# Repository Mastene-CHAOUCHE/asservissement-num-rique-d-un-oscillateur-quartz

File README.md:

# asservissement-num-rique-d-un-oscillateur-quartz

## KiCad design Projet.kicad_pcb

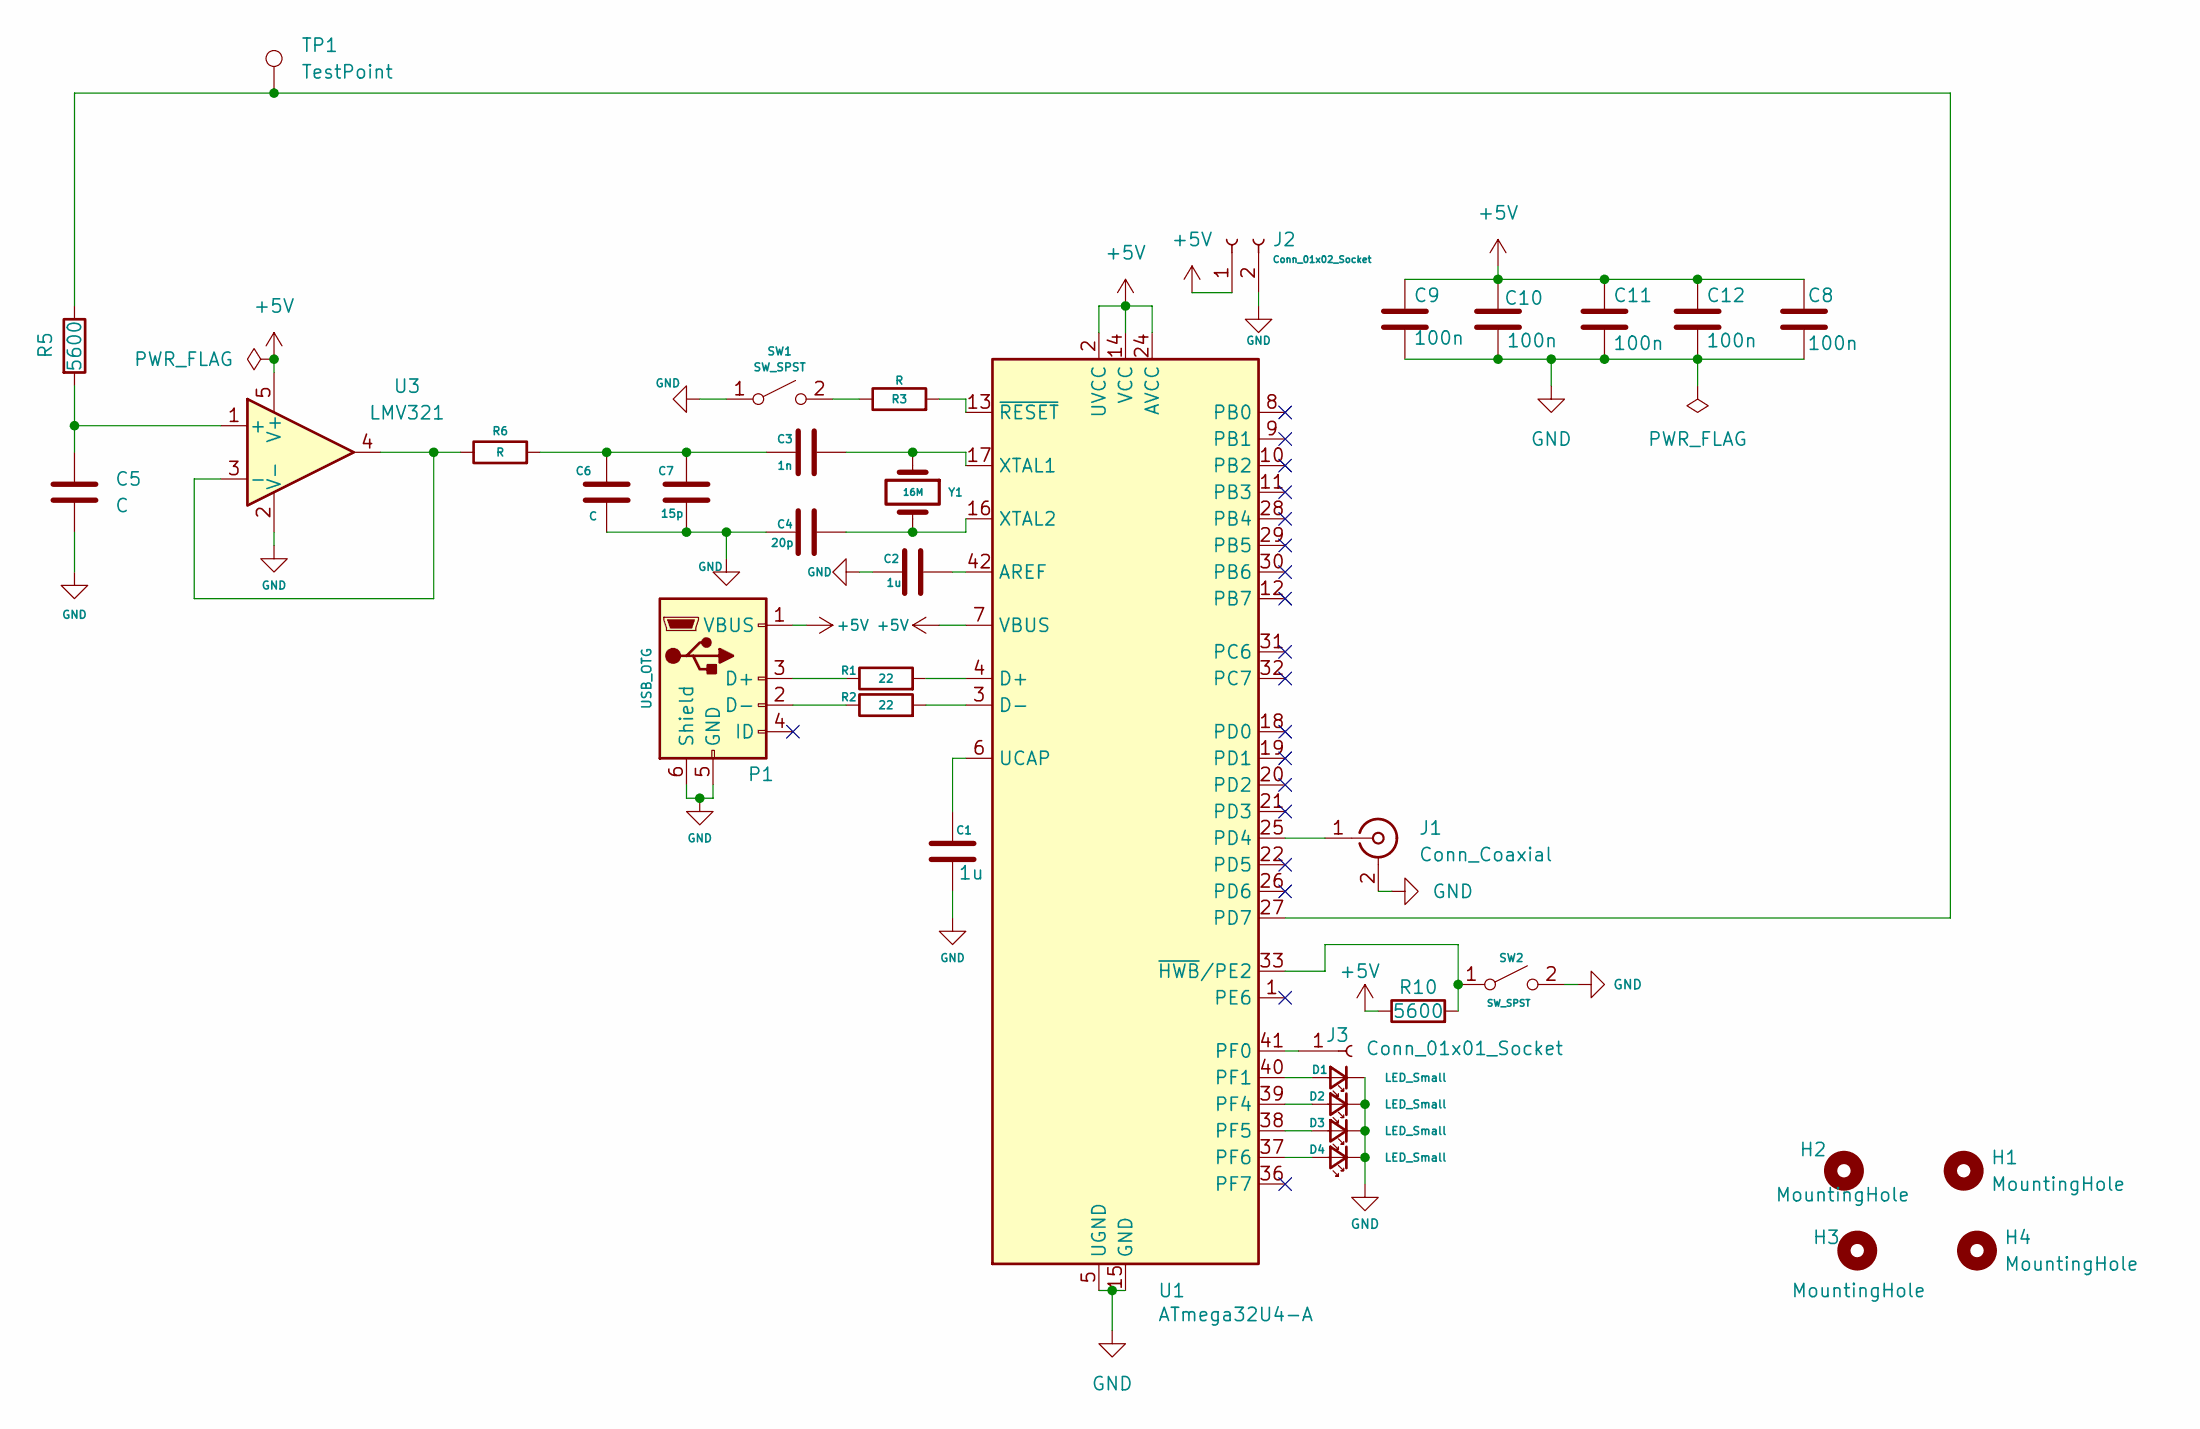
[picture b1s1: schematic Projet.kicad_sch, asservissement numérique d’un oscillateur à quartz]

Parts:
C1, C2: 1u; C_0805_2012Metric_Pad1.18x1.45mm_HandSolder
C3: 1n; C_0805_2012Metric_Pad1.18x1.45mm_HandSolder
C4: 20p; C_0805_2012Metric_Pad1.18x1.45mm_HandSolder
C5, C6: C; C_0805_2012Metric_Pad1.18x1.45mm_HandSolder
C7: 15p; C_0805_2012Metric_Pad1.18x1.45mm_HandSolder
C8, C9, C10, C11, C12: 100n; C_0805_2012Metric_Pad1.18x1.45mm_HandSolder
D1, D2, D3, D4: LED_Small; LED_1206_3216Metric_Pad1.42x1.75mm_HandSolder
H1, H2, H3, H4: MountingHole; MountingHole_3mm
J1: Conn_Coaxial; SMA_Amphenol_132134_Vertical
J2: Conn_01x02_Socket; PinHeader_1x02_P2.54mm_Vertical
J3: Conn_01x01_Socket; PinHeader_1x01_P2.54mm_Vertical
P1: USB_OTG; USB_Mini-B_Lumberg_2486_01_Horizontal
R1, R2: 22; R_0805_2012Metric_Pad1.20x1.40mm_HandSolder
R3, R6: R; R_0805_2012Metric_Pad1.20x1.40mm_HandSolder
R5, R10: 5600; R_0805_2012Metric_Pad1.20x1.40mm_HandSolder
SW1, SW2: SW_SPST; SW_PUSH_6mm
TP1: TestPoint; TestPoint_Pad_1.0x1.0mm
U1: ATmega32U4-A; TQFP-44_10x10mm_P0.8mm
U3: LMV321; SOT-23-5_HandSoldering
Y1: 16M; Crystal_SMD_5032-2Pin_5.0x3.2mm_HandSoldering

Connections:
+5V: C8.1, C9.1, C10.1, C11.1, C12.1, J2.1, P1.1 (VBUS), R10.1, U1.2 (UVCC), U1.7 (VBUS), U1.14 (VCC), U1.24 (AVCC), U1.34 (VCC), U1.44 (AVCC), U3.5 (V+)
GND: C1.2, C2.1, C4.1, C5.2, C6.2, C7.2, C8.2, C9.2, C10.2, C11.2, C12.2, D1.1 (K), D2.1 (K), D3.1 (K), D4.1 (K), J1.2 (Ext), J2.2, P1.5 (GND), P1.6 (Shield), SW1.1 (A), SW2.2 (B), U1.5 (UGND), U1.15 (GND), U1.23 (GND), U1.35 (GND), U1.43 (GND), U3.2 (V-)
unnamed: C3.2, C6.1, C7.1, R6.2
unnamed: D1.2 (A), U1.40 (PF1)
unnamed: D2.2 (A), U1.39 (PF4)
unnamed: D3.2 (A), U1.38 (PF5)
unnamed: D4.2 (A), U1.37 (PF6)
unnamed: J1.1 (In), U1.25 (PD4)
unnamed: J3.1, U1.41 (PF0)
unnamed: P1.3 (D+), R1.1
unnamed: P1.2 (D-), R2.1
unnamed: R3.1, SW1.2 (B)
unnamed: R10.2, SW2.1 (A), U1.33 (~HWB/PE2)
unnamed: C2.2, U1.42 (AREF)
unnamed: R1.2, U1.4 (D+)
unnamed: R2.2, U1.3 (D-)
unnamed: R5.1, TP1.1, U1.27 (PD7)
unnamed: C1.1, U1.6 (UCAP)
unnamed: C3.1, U1.17 (XTAL1), Y1.1
unnamed: C4.2, U1.16 (XTAL2), Y1.2
unnamed: R3.2, U1.13 (~RESET)
unnamed: C5.1, R5.2, U3.1 (+)
unnamed: R6.1, U3.3 (-), U3.4

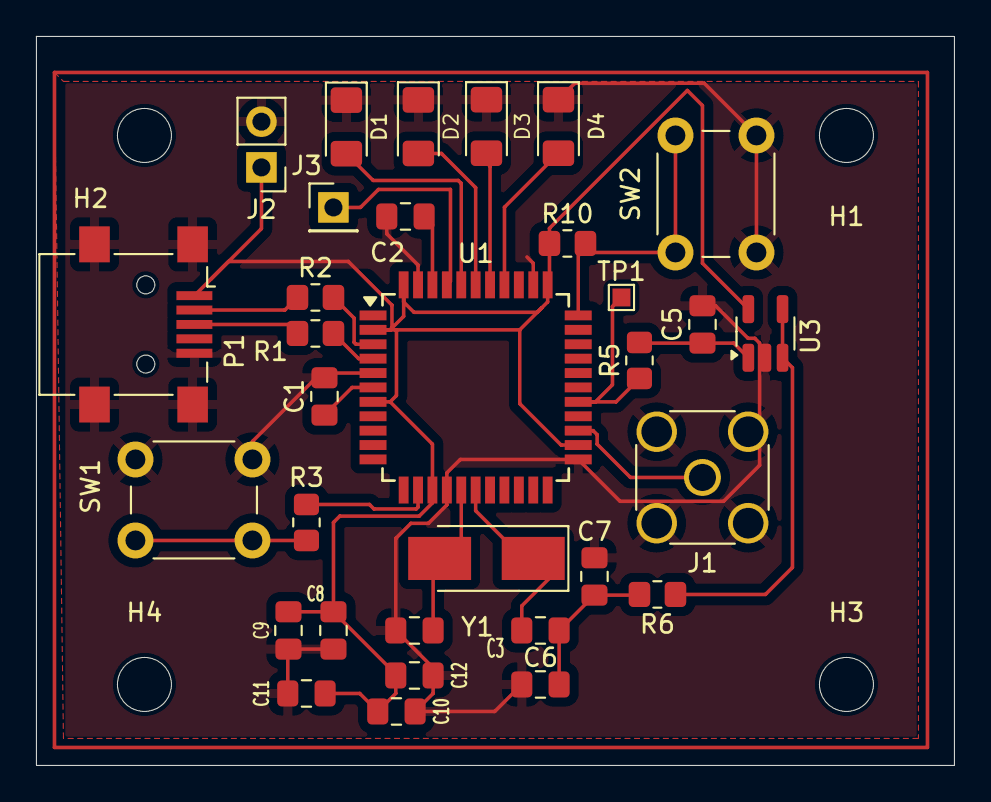
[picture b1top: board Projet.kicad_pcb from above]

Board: 2 copper layers, 51.0 x 40.5 mm, 36 parts (0 on the bottom side), 23 nets.

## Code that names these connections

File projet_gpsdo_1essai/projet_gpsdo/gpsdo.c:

#define F_CPU 16000000UL
#include <avr/io.h> //E/S ex PORTB
#include <util/delay.h>
#include "VirtualSerial.h"

int main(void){
    MCUCR |= (1 << JTD);
    MCUCR |= (1 << JTD);
    SetupHardware();

    DDRF |= (1 << PF1);   
    DDRF |= (1 << PF4);   
    DDRF |= (1 << PF5);   
    DDRF |= (1 << PF6); 

    while(1)
    {
        /* Allumer toutes les LEDs */
        PORTF |= (1 << PF1);
        PORTF |= (1 << PF4);
        PORTF |= (1 << PF5);
        PORTF |= (1 << PF6);
        _delay_ms(500);
        /* Eteindre toutes les LEDs */
        PORTF &= ~(1 << PF1);
        PORTF &= ~(1 << PF4);
        PORTF &= ~(1 << PF5);
        PORTF &= ~(1 << PF6);
        _delay_ms(500);
    }

    return 0;
}

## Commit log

2026-03-26 BOM KiCad + liste des composants
    Ajout du BOM KiCad et du PDF des composants (fournisseur : Mouser)
2026-03-26 Ajout du schéma et du PCB KiCad
2026-03-26 Shéma et pcd Kicad
2026-03-26 Ajout du BOM KiCad et du PDF des composants (fournisseur : Mouser)
